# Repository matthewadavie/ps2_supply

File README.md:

# PS2 Supply
## Background
I had a friend ask about how to supply a PS2 from his car. Originally he wanted buy an inverter to run off an accessory port, then run the standard PS2 AC-DC adaptor. This is a workaround, that is (hopefully) significantly more efficient.

## Requirements
* Input Voltage: 6V - 18V (nominal)
* Input Voltage: 4V - 30V (transient)
* Output Voltage: 8.5V @ 1A (ish)

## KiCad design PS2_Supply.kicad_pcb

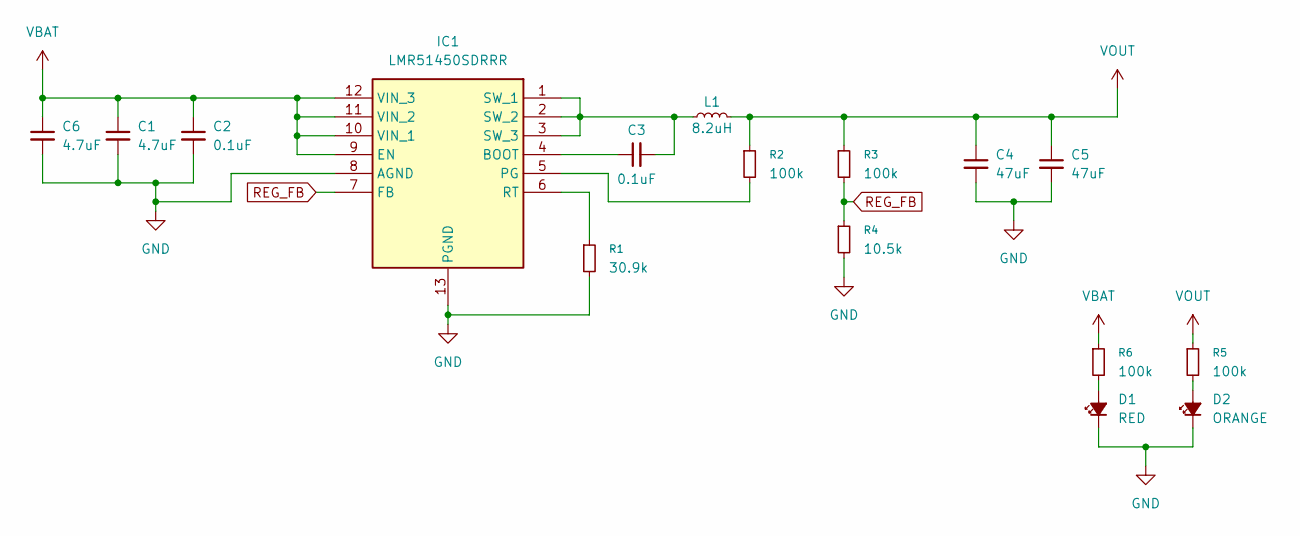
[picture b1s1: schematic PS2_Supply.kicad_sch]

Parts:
C1, C6: 4.7uF; C_0805_2012Metric_Pad1.18x1.45mm_HandSolder
C2, C3: 0.1uF; C_0805_2012Metric_Pad1.18x1.45mm_HandSolder
C4, C5: 47uF; C_0805_2012Metric_Pad1.18x1.45mm_HandSolder
D1: RED; LED_0805_2012Metric_Pad1.15x1.40mm_HandSolder
D2: ORANGE; LED_0805_2012Metric_Pad1.15x1.40mm_HandSolder
IC1: LMR51450SDRRR; SON50P300X300X80-13N-D; Manufacturer_Part_Number LMR51450SDRRR; Mouser Part Number 595-LMR51450SDRRR
L1: 8.2uH; L_Coilcraft_XAL6060-XXX
R1: 30.9k; R_0805_2012Metric_Pad1.20x1.40mm_HandSolder
R2, R3, R5, R6: 100k; R_0805_2012Metric_Pad1.20x1.40mm_HandSolder
R4: 10.5k; R_0805_2012Metric_Pad1.20x1.40mm_HandSolder

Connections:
GND: C1.2, C2.2, C4.2, C5.2, C6.2, D1.1 (K), D2.1 (K), IC1.8 (AGND), IC1.13 (PGND), R1.2, R4.2
unnamed: D1.2 (A), R6.2
unnamed: D2.2 (A), R5.2
unnamed: C3.1, IC1.4 (BOOT)
unnamed: IC1.5 (PG), R2.2
unnamed: IC1.6 (RT), R1.1
unnamed: C3.2, IC1.1 (SW_1), IC1.2 (SW_2), IC1.3 (SW_3), L1.1
REG_FB: IC1.7 (FB), R3.2, R4.1
VBAT: C1.1, C2.1, C6.1, IC1.9 (EN), IC1.10 (VIN_1), IC1.11 (VIN_2), IC1.12 (VIN_3), R6.1
VOUT: C4.1, C5.1, L1.2, R2.1, R3.1, R5.1

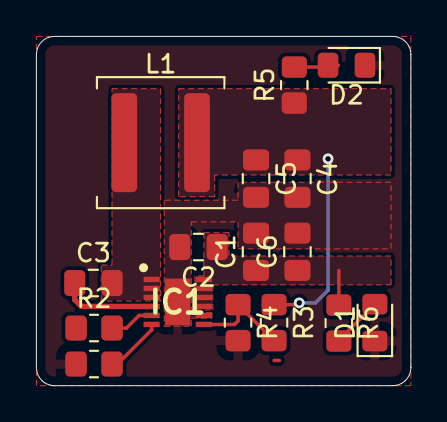
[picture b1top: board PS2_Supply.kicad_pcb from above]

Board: 2 copper layers, 20.8 x 19.4 mm, 16 parts (0 on the bottom side), 10 nets.

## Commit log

2026-01-14 Adding readme.
